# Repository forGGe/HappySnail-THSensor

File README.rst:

############################################################################
Happy Snail TH-Sensor: RS-485 ModBus Digital Temperature and Humidity Sensor
############################################################################

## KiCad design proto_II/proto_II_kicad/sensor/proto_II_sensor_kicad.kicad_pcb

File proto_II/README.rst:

###################################
Happy Snail TH-Sensor: Prototype II
###################################

*********************
Generating proper BOM
*********************

#. Install `KiBOM`_ tool. Instructions below assume that it was installed under ``~/project/KiBoM``
   directory.

#. Install `Interactive BOM tool`_. Instructions below assume that it was installed under
   ``~/projects/InteractiveHtmlBom/`` directory.

#. Generate `proto_II_assembly.xml` file by exporting any BOM from the KiCAD eeschema. This intermediate
   file is required for futher processing and there is no way to generate it without generating
   default KiCAD BOM.

#. Run from within ``proto_II_kicad/assembly`` directory::

     # Generic variant
     ~/projects/KiBoM/KiBOM_CLI.py ./proto_II_assembly.xml ./bom.csv

     # Only 5V, non-isolated RS485 variant
     ~/projects/KiBoM/KiBOM_CLI.py -r noiso_5v ./proto_II_assembly.xml ./bom.csv

     # Better 12V-24V, isolated RS485 variant
     ~/projects/KiBoM/KiBOM_CLI.py -r iso_12_24v ./proto_II_assembly.xml ./bom.csv

#. Generate BOM for importing into PartsBox::

     python ../../../scripts/process_bom.py ./bom.csv ./partsbox_bom.csv

#. Run from within ``proto_II_kicad/assembly`` directory to generate interactive BOM::

     python ~/projects/InteractiveHtmlBom/InteractiveHtmlBom/generate_interactive_bom.py \
       ./proto_II_assembly.kicad_pcb   \
       --netlist-file ./proto_II_assembly.xml \
       --extra-fields "MPN"

.. _`KiBOM`: https://github.com/SchrodingersGat/KiBoM
.. _`Interactive BOM tool`: https://github.com/openscopeproject/InteractiveHtmlBom

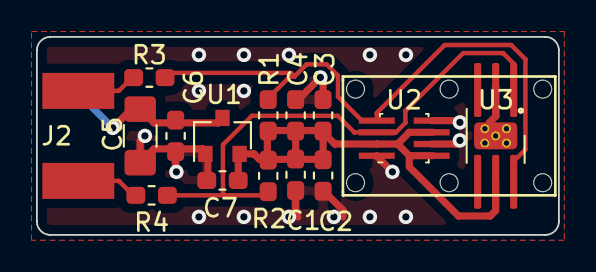
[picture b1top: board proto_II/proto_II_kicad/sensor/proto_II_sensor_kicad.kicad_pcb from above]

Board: 2 copper layers, 29.0 x 11.0 mm, 16 parts (1 on the bottom side), 7 nets.

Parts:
C1, C4: 100n; C_0603_1608Metric_Pad1.05x0.95mm_HandSolder
C2, C3: 10n; C_0603_1608Metric_Pad1.05x0.95mm_HandSolder
C5: 10u; C_1206_3216Metric_Pad1.42x1.75mm_HandSolder
C6, C7: 1u; C_0603_1608Metric_Pad1.05x0.95mm_HandSolder
J1, J2: Conn_01x02; PAD_2
R1, R2: 4K7; R_0603_1608Metric_Pad1.05x0.95mm_HandSolder
R3, R4: TERM; R_0603_1608Metric_Pad1.05x0.95mm_HandSolder
U1: XC6206P332MR; SOT-23
U2: BME280; Bosch_LGA-8_2.5x2.5mm_P0.65mm_ClockwisePinNumbering_HandSol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
U3: Si7020-A20; DFN-6-1EP_3x3mm_P1mm_EP1.5x2.4mm_HandSoldering

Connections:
+3V3: C1.1, C2.1, C3.1, C4.1, C7.1, R1.1, R2.1, U1.2, U2.2, U2.6, U2.8, U3.5
+5V: C5.1, C6.1, J1.1, U1.3
/SCL: J2.1, R3.1
/SCL_IC: R1.2, R3.2, U2.4, U3.6
/SDA: J2.2, R4.1
/SDA_IC: R2.2, R4.2, U2.3, U3.1
GND: C1.2, C2.2, C3.2, C4.2, C5.2, C6.2, C7.2, J1.2, U1.1, U2.1, U2.5, U2.7, U3.2, U3.7

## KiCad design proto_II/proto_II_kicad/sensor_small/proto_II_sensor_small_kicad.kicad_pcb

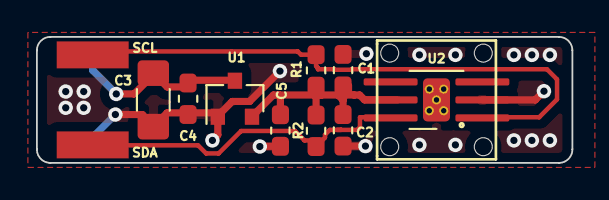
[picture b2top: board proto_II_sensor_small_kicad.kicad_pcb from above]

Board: 2 copper layers, 29.8 x 7.0 mm, 11 parts (1 on the bottom side), 5 nets.

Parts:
C1: 100n; C_0603_1608Metric_Pad1.05x0.95mm_HandSolder
C2: 10n; C_0603_1608Metric_Pad1.05x0.95mm_HandSolder
C3: 10u; C_1206_3216Metric_Pad1.42x1.75mm_HandSolder
C4, C5: 1u; C_0603_1608Metric_Pad1.05x0.95mm_HandSolder
J1: PWR_CONN; PAD_2_small
J2: I2C_CONN; PAD_2_small
R1, R2: 4K7; R_0603_1608Metric_Pad1.05x0.95mm_HandSolder
U1: XC6206P332MR; SOT-23
U2: Si7020-A20; DFN-6-1EP_3x3mm_P1mm_EP1.5x2.4mm_HandSoldering

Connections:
+3V3: C1.1, C2.1, C5.1, R1.1, R2.1, U1.2, U2.5
+5V: C3.1, C4.1, J1.1, U1.3
/SCL: J2.1, R1.2, U2.1
/SDA: J2.2, R2.2, U2.6
GND: C1.2, C2.2, C3.2, C4.2, C5.2, J1.2, U1.1, U2.2, U2.7

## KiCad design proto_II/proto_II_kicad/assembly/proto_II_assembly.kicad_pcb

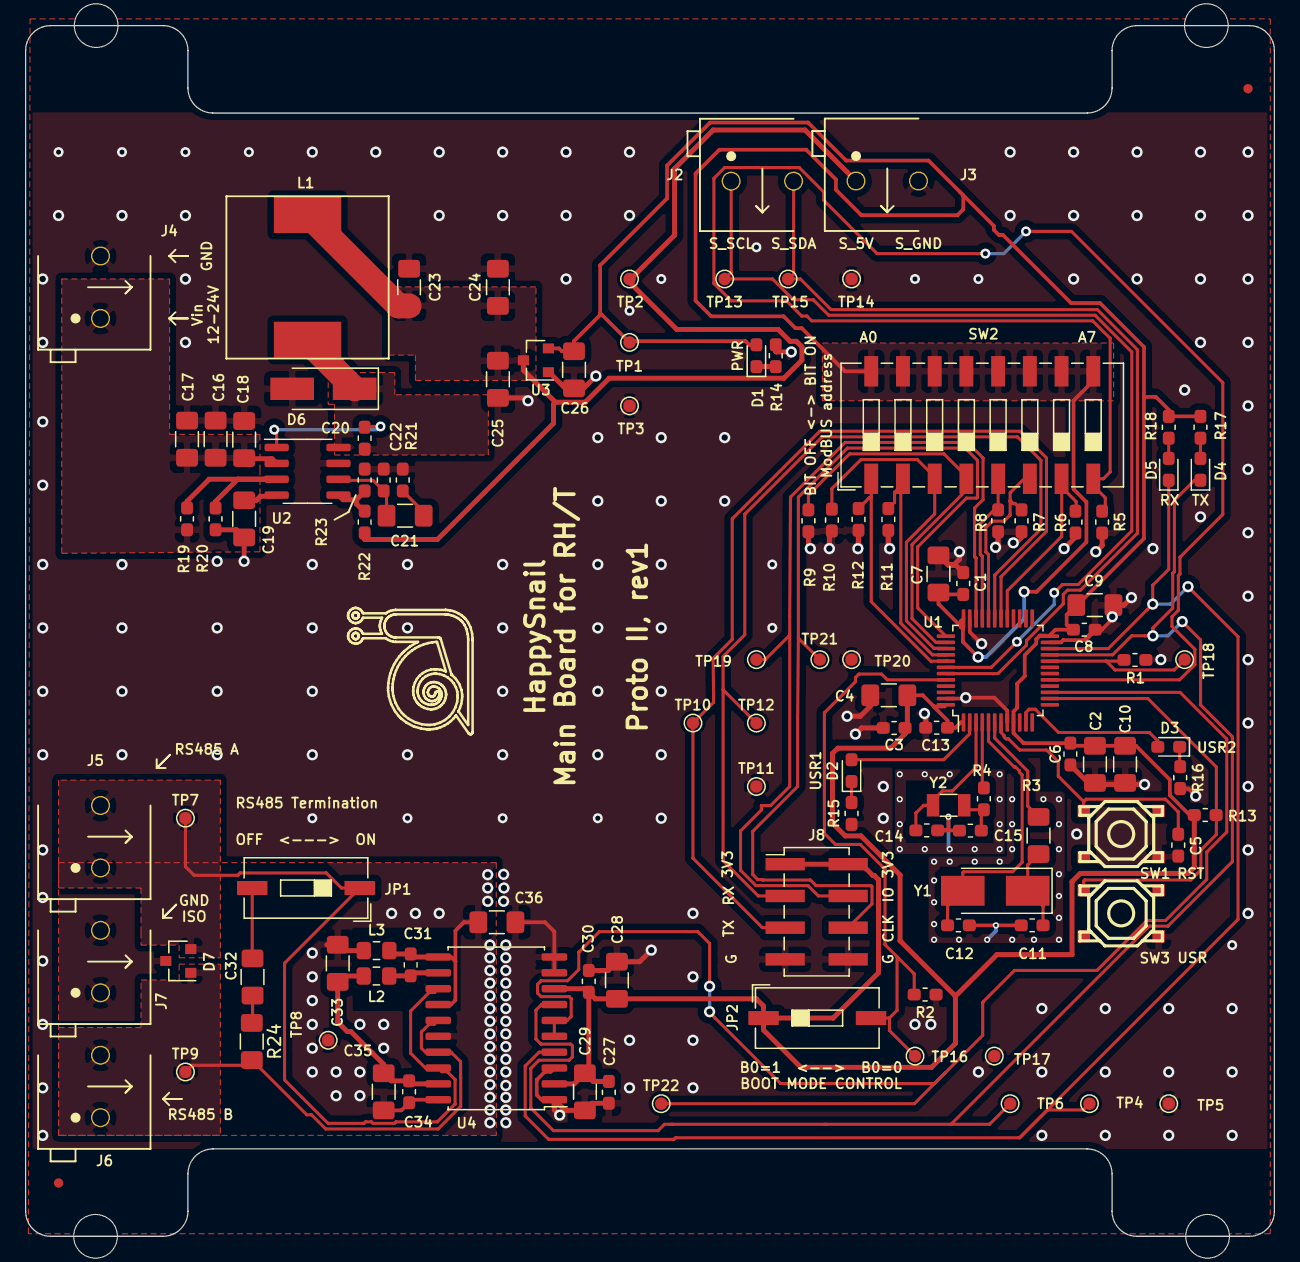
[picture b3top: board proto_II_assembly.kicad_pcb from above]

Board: 2 copper layers, 100.0 x 97.0 mm, 110 parts (0 on the bottom side), 52 nets.

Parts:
C1, C3, C5, C6, C8, C13, C20, C27, C30, C31, C34: 100n; C_0603_1608Metric_Pad1.05x0.95mm_HandSolder
C2, C4, C7, C9, C10, C25, C26: 1u; C_1206_3216Metric_Pad1.42x1.75mm_HandSolder
C11, C12: 30p; C_0603_1608Metric_Pad1.05x0.95mm_HandSolder
C14, C15, C22: 10p; C_0603_1608Metric_Pad1.05x0.95mm_HandSolder
C16, C17, C23, C24, C28, C33: 10u; C_1206_3216Metric_Pad1.42x1.75mm_HandSolder
C18, C19, C21, C29, C32, C35, C36: 10n; C_1206_3216Metric_Pad1.42x1.75mm_HandSolder
D1, D2, D3, D4, D5: BLUE_LED; D_0603_1608Metric_Pad1.05x0.95mm_HandSolder
D6: 700mV; D_SMA_Handsoldering
D7: SM712; SOT-23
J2: SNSR_I2C; DG300-5.0-02P-12
J3: SNSR_PWR; DG300-5.0-02P-12
J4: Vin; DG300-5.0-02P-12
J5: RS485_A; DG300-5.0-02P-12
J6: RS485_B; DG300-5.0-02P-12
J7: ISO_GND; DG300-5.0-02P-12
J8: SWD_DBG; PinHeader_2x04_P2.54mm_Vertical_SMD
JP1, JP2: JP; SW_DIP_SPSTx01_Slide_9.78x4.72mm_W8.61mm_P2.54mm
L1: 47u; SWRB1205S
L2, L3: FB; L_0805_2012Metric_Pad1.15x1.40mm_HandSolder
R1, R2, R5, R6, R7, R8, R9, R10, R11, R12, R13, R21, R22: 10K; R_0603_1608Metric_Pad1.05x0.95mm_HandSolder
R3: 560; R_1206_3216Metric_Pad1.42x1.75mm_HandSolder
R4: 0R; R_0603_1608Metric_Pad1.05x0.95mm_HandSolder
R14, R15, R16, R17, R18, R23: 2K2; R_0603_1608Metric_Pad1.05x0.95mm_HandSolder
R19: 220K; R_0603_1608Metric_Pad1.05x0.95mm_HandSolder
R20: 47K; R_0603_1608Metric_Pad1.05x0.95mm_HandSolder
R24: 120; R_1206_3216Metric_Pad1.42x1.75mm_HandSolder
SW1, SW3: PB; Tactile_Switch_5x5mm
SW2: MODBUS_ADDR; SW_DIP_SPSTx08_Slide_9.78x22.5mm_W8.61mm_P2.54mm
TP1: 3V3; TestPoint_Pad_D1.0mm
TP2: 5V; TestPoint_Pad_D1.0mm
TP3: G; TestPoint_Pad_D1.0mm
TP4: U2_RX; TestPoint_Pad_D1.0mm
TP5: G_U2; TestPoint_Pad_D1.0mm
TP6: U2_TX; TestPoint_Pad_D1.0mm
TP7: A; TestPoint_Pad_D1.0mm
TP8: G_ISO; TestPoint_Pad_D1.0mm
TP9: B; TestPoint_Pad_D1.0mm
TP10: U1_RX; TestPoint_Pad_D1.0mm
TP11, TP17, TP20: G_U1; TestPoint_Pad_D1.0mm
TP12: U1_TX; TestPoint_Pad_D1.0mm
TP13: SCL; TestPoint_Pad_D1.0mm
TP14: G_I2C; TestPoint_Pad_D1.0mm
TP15: SDA; TestPoint_Pad_D1.0mm
TP16, TP19: U1_B0; TestPoint_Pad_D1.0mm
TP18, TP21: U1_B1; TestPoint_Pad_D1.0mm
TP22: DE_RE; TestPoint_Pad_D1.0mm
U1: STM32F103C8Tx; LQFP-48_7x7mm_P0.5mm
U2: TPS54331; SOIC-8_3.9x4.9mm_P1.27mm
U3: XC6206P332MR; SOT-23
U4: ADM2587E; SOIC-20W_7.5x12.8mm_P1.27mm
Y1: HSE; Crystal_SMD_5032-2Pin_5.0x3.2mm_HandSoldering
Y2: LSE; Crystal_SMD_3215-2Pin_3.2x1.5mm

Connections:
+3V3: C1.1, C2.1, C3.1, C4.1, C6.1, C7.1, C8.1, C9.1, C10.1, C13.1, C26.1, C27.1, C28.1, C29.1, C30.1, D1.2, J8.1, J8.2, JP2.1, R13.2, R17.2, R18.2, SW2.9, SW2.10, SW2.11, SW2.12, SW2.13, SW2.14, SW2.15, SW2.16, TP1.1, U1.1, U1.9, U1.24, U1.36, U1.48, U3.2, U4.2, U4.8
+5V: C23.1, C24.1, C25.1, J3.1, L1.2, R22.1, TP2.1, U3.3
/BOOT0: JP2.2, R2.2, TP16.1, U1.44
/BOOT1: R1.1, TP18.1, U1.20
/DE~RE: TP22.1, U1.15, U4.5, U4.6
/I2C1_SCL: J2.1, TP13.1, U1.42
/I2C1_SDA: J2.2, TP15.1, U1.43
/MODBUS_A0: R12.1, SW2.1, U1.41
/MODBUS_A1: R11.1, SW2.2, U1.40
/MODBUS_A2: R10.1, SW2.3, U1.39
/MODBUS_A3: R9.1, SW2.4, U1.38
/MODBUS_A4: R8.1, SW2.5, U1.33
/MODBUS_A5: R7.1, SW2.6, U1.32
/MODBUS_A6: R6.1, SW2.7, U1.29
/MODBUS_A7: R5.1, SW2.8, U1.17
/NRST: C5.1, SW1.2, U1.7
/OSC32_IN: C14.2, U1.3, Y2.1
/OSC32_OUT: R4.1, U1.4
/OSC_IN: C12.1, U1.5, Y1.2
/OSC_OUT: R3.1, U1.6
/RS485_A: D7.2, J5.1, J5.2, JP1.1, TP7.1, U4.13, U4.18
/RS485_B: D7.1, J6.1, J6.2, R24.2, TP9.1, U4.15, U4.17
/SWDCLK: J8.6, TP21.1, U1.37
/SWDIO: J8.4, TP19.1, U1.34
/UART1_RX: J8.3, TP12.1, U1.31
/UART1_TX: J8.5, TP10.1, U1.30
/UART3_RX: D5.1, TP4.1, U1.22, U4.4
/UART3_TX: D4.1, TP6.1, U1.21, U4.7
/USR1_LED: D2.2, U1.2
/USR2_LED: D3.2, U1.11
/USR_BTN: R13.1, SW3.2, U1.14
/power/PH: C20.1, D6.1, L1.1, U2.8
/power/Vin: C16.1, C17.1, C18.1, J4.1, R19.1, U2.2
/rs485/ISO_IN: C33.1, C34.1, C35.1, L2.2, U4.19
/rs485/ISO_OUT: C31.1, L2.1, U4.12
GND: C1.2, C2.2, C3.2, C4.2, C5.2, C6.2, C7.2, C8.2, C9.2, C10.2, C11.2, C12.2, C13.2, C14.1, C15.1, C16.2, C17.2, C18.2, C19.2, C22.2, C23.2, C24.2, C25.2, C26.2, C27.2, C28.2, C29.2, C30.2, C36.1, D6.2, J3.2, J4.2, J8.7, J8.8, R1.2, R2.1, R5.2, R6.2, R7.2, R8.2, R9.2, R10.2, R11.2, R12.2, R14.2, R15.2, R16.2, R20.2, R21.2, R23.2, SW1.1, SW3.1, TP3.1, TP5.1, TP11.1, TP14.1, TP17.1, TP20.1, U1.8, U1.23, U1.35, U1.47, U2.7, U3.1, U4.1, U4.3, U4.9, U4.10
GNDD: C31.2, C33.2, C34.2, C35.2, C36.2, D7.3, J7.1, J7.2, L3.1, L3.2, TP8.1, U4.11, U4.14, U4.16, U4.20
unnamed: C11.1, R3.2, Y1.1
unnamed: C15.2, R4.2, Y2.2
unnamed: C19.1, U2.4
unnamed: C20.2, U2.1
unnamed: C21.1, C22.1, U2.6
unnamed: C21.2, R21.1
unnamed: C32.1, R24.1
unnamed: C32.2, JP1.2
unnamed: D1.1, R14.1
unnamed: D2.1, R15.1
unnamed: D3.1, R16.1
unnamed: D4.2, R17.1
unnamed: D5.2, R18.1
unnamed: R19.2, R20.1, U2.3
unnamed: R22.2, R23.1, U2.5

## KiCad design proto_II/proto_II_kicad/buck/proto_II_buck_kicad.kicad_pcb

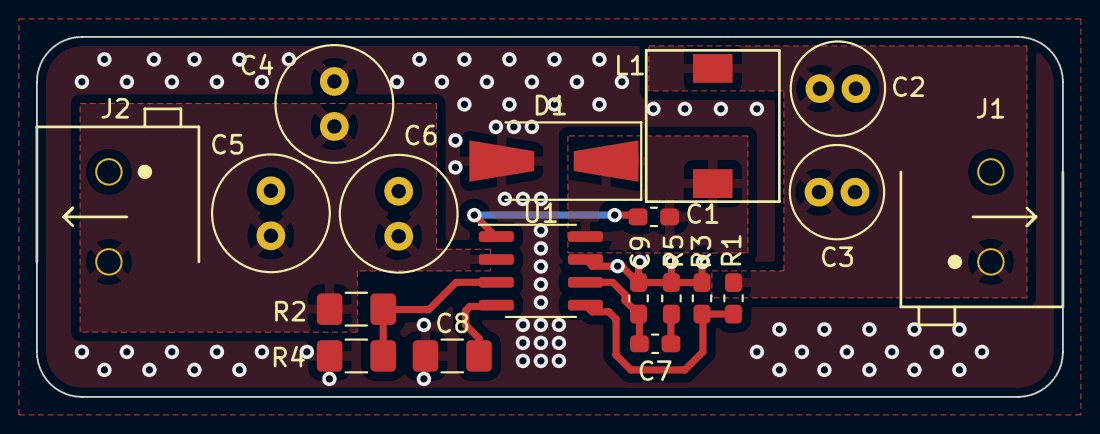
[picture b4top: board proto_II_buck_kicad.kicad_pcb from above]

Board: 2 copper layers, 57.0 x 20.0 mm, 19 parts (0 on the bottom side), 10 nets.

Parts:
C1: 100n; C_0603_1608Metric_Pad1.05x0.95mm_HandSolder
C2, C3: 47u; C_Radial_D5.0mm_H11.0mm_P2.00mm
C4, C5: 10u; C_Radial_D6.3mm_H11.0mm_P2.50mm
C6: 10n; C_Radial_D6.3mm_H11.0mm_P2.50mm
C7: 2n2; C_0603_1608Metric_Pad1.05x0.95mm_HandSolder
C8: 10n; C_1206_3216Metric_Pad1.42x1.75mm_HandSolder
C9: 10p; C_0603_1608Metric_Pad1.05x0.95mm_HandSolder
D1: 700mV; D_SMA-SMB_Universal_Handsoldering
J1: VDC_OUT; DG300-5.0-02P-12
J2: VDC_IN; DG300-5.0-02P-12
L1: 22u; CDRH74
R1: 10K; R_0603_1608Metric_Pad1.05x0.95mm_HandSolder
R2: 220K; R_1206_3216Metric_Pad1.42x1.75mm_HandSolder
R3: 2K2; R_0603_1608Metric_Pad1.05x0.95mm_HandSolder
R4: 47K; R_1206_3216Metric_Pad1.42x1.75mm_HandSolder
R5: 13K3; R_0603_1608Metric_Pad1.05x0.95mm_HandSolder
U1: TPS54331; SOIC-8_3.9x4.9mm_P1.27mm

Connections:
/PH: C1.1, D1.1, L1.1, U1.8
/VIN: C4.1, C5.1, C6.1, J2.2, R2.1, U1.2
/VOUT: C2.1, C3.1, J1.1, L1.2, R1.1
GND: C2.2, C3.2, C4.2, C5.2, C6.2, C8.2, C9.2, D1.2, J1.2, J2.1, R3.2, R4.2, R5.2, U1.7
unnamed: C1.2, U1.1
unnamed: C7.1, C9.1, U1.6
unnamed: C7.2, R5.1
unnamed: C8.1, U1.4
unnamed: R1.2, R3.1, U1.5
unnamed: R2.2, R4.1, U1.3

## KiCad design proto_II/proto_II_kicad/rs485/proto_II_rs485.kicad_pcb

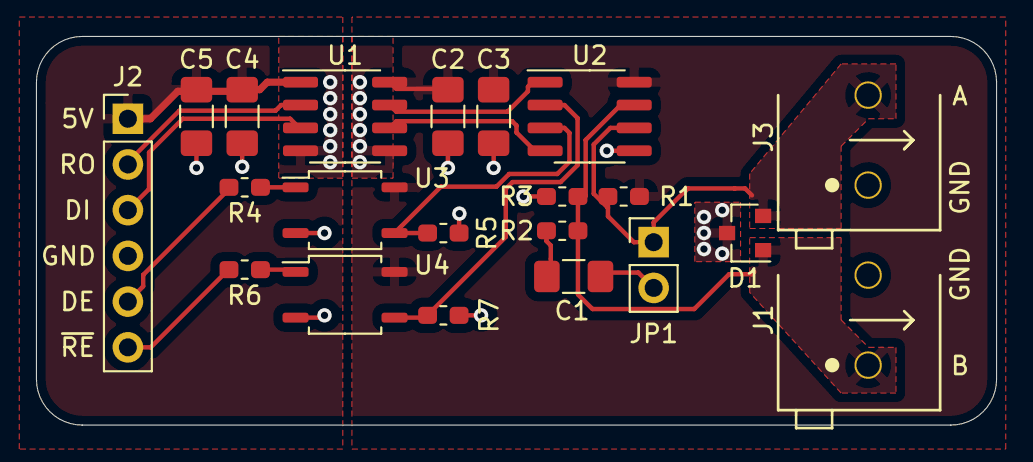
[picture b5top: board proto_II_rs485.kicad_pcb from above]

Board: 2 copper layers, 53.3 x 21.6 mm, 21 parts (0 on the bottom side), 18 nets.

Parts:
C1: 10n; C_1206_3216Metric_Pad1.42x1.75mm_HandSolder
C2, C4: 100n; C_1206_3216Metric_Pad1.42x1.75mm_HandSolder
C3, C5: 1u; C_1206_3216Metric_Pad1.42x1.75mm_HandSolder
D1: SM712; SOT-23
J1: A_CONN; DG300-5.0-02P-12
J2: INPUT; PinHeader_1x06_P2.54mm_Vertical
J3: B_CONN; DG300-5.0-02P-12
JP1: JP; PinHeader_1x02_P2.54mm_Vertical
R1, R3, R4, R6: 2K2; R_0603_1608Metric_Pad1.05x0.95mm_HandSolder
R2: 120; R_0603_1608Metric_Pad1.05x0.95mm_HandSolder
R5, R7: 10K; R_0603_1608Metric_Pad1.05x0.95mm_HandSolder
U1: ADUM5241; SOIC-8_3.9x4.9mm_P1.27mm
U2: ST485EBDR; SOIC-8_3.9x4.9mm_P1.27mm
U3, U4: EL357N-G; SOP-4_3.8x4.1mm_P2.54mm

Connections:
+5V: C4.1, C5.1, J2.1, U1.1
+5VD: C2.1, C3.1, R1.2, U1.8, U2.8, U3.4, U4.4
/A: D1.2, J3.2, JP1.1, R1.1, U2.6
/B: D1.1, J1.1, R2.2, R3.2, U2.7
/DE: J2.5, R4.2
/DI: J2.3, U1.3
/RO: J2.2, U1.2
/~RE: J2.6, R6.2
GND: C4.2, C5.2, J2.4, U1.4, U3.2, U4.2
GNDD: C2.2, C3.2, D1.3, J1.2, J3.1, R3.1, R5.1, R7.1, U1.5, U2.5
unnamed: C1.1, R2.1
unnamed: C1.2, JP1.2
unnamed: R4.1, U3.1
unnamed: R5.2, U2.3, U3.3
unnamed: R6.1, U4.1
unnamed: R7.2, U2.2, U4.3
unnamed: U1.6, U2.4
unnamed: U1.7, U2.1

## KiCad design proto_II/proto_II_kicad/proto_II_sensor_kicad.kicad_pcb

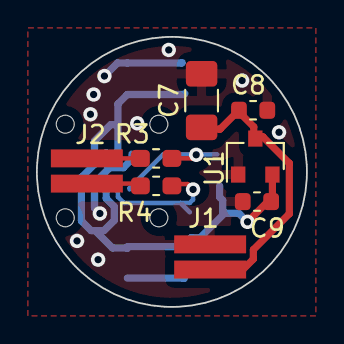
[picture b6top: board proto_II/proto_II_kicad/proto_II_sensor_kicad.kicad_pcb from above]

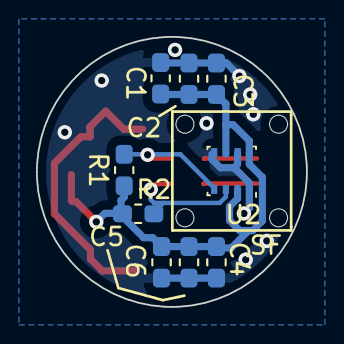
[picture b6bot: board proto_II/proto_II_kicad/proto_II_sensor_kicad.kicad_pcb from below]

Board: 2 copper layers, 15.0 x 15.0 mm, 18 parts (10 on the bottom side), 7 nets.

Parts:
C1, C6: 1u; C_0603_1608Metric_Pad1.05x0.95mm_HandSolder
C2, C5: 100n; C_0603_1608Metric_Pad1.05x0.95mm_HandSolder
C3, C4: 10n; C_0603_1608Metric_Pad1.05x0.95mm_HandSolder
C7: 10u; C_1206_3216Metric_Pad1.42x1.75mm_HandSolder
C8, C9: 1u; C_0603_1608Metric
J1, J2: Conn_01x02; PAD_2
R1, R2: 4K7; R_0603_1608Metric_Pad1.05x0.95mm_HandSolder
R3, R4: TERM; R_0603_1608Metric_Pad1.05x0.95mm_HandSolder
SF: SF2-CAP; SENSIRION-SF2
U1: XC6206P332MR; SOT-23
U2: BME280; Bosch_LGA-8_2.5x2.5mm_P0.65mm_ClockwisePinNumbering

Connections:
+3V3: C1.1, C2.1, C3.1, C4.1, C5.1, C6.1, C9.1, R1.1, R2.1, U1.2, U2.2, U2.6, U2.8
+5V: C7.1, C8.1, J1.1, U1.3
GND: C1.2, C2.2, C3.2, C4.2, C5.2, C6.2, C7.2, C8.2, C9.2, J1.2, U1.1, U2.1, U2.5, U2.7
unnamed: J2.1, R3.1
unnamed: J2.2, R4.1
unnamed: R1.2, R3.2, U2.4
unnamed: R2.2, R4.2, U2.3

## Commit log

2019-06-16 Add prototype I subproject tree and basic schematic
2019-06-16 PC13 blink code
2019-06-16 RS485 reading and writing
2019-06-19 Zephyr-based BAT placeholder
    Previous stuff moved to .attic
2019-06-21 Extended BAT with rough modbus ASCII parser
2019-06-23 Complete BAT code
2019-06-23 Complete BAT schematics
2019-06-30 Proto II: basic circuit around TPS54331, not computed yet
    Values of components to be computed later.
2019-07-02 Re-wire switching power supply and add sensor sub-project
    Switching regulator re-wired according to guidelines.
    Still, freq compensation values must be re-calculated.
    Sensor sub-project is added. Its purpose to deliver small PCB
    board, where sensor is soldered and sealed.
2019-07-07 Proto II: route for sensor board
    Add libraries and footprints for SF2 cap and simple PAD connector for
    soldering wires
2019-07-09 Proto II: route buck converter sub-board
    Additionally:
    - Made footprint for inductor and found 3d-model for that
    - Add missing PCB and netlist for sensor sub-board (see previous commit)
    - Couple of addtions for existing footprints (SF2, PAD, etc.)A
    - Update gitignore to ignore cache KiCAD files
2019-07-09 Proto II: panelized sensor and buck board, order from JLCPCB
    + gerber files
2019-07-12 Proto II: cleanup and move project to separate dirs
    Common library is substituted. Gerber files are updated to match what
    sent to JLCPCB
2019-07-17 Proto II: RS485 isolated module board
2019-07-18 Proto II: RS485 isolated module board, order from JLCPCB
2019-08-08 Capture real part information into the schematic
2019-08-16 Rework sensor board: allow hand-soldering of sensor
    Additional sensor is used with easier footprint: Si70XX series
2019-08-17 Rework sensor board: gerber files
2019-08-17 Fix bug: spurious character led to infinite ModBus response
    + add script to read values and send them to TB
2019-09-16 8mm sensor PCB
2019-09-16 BAT code for Si7006
2019-09-18 Update instructions on flashing and using board for BAT tests
2019-09-19 Fix table rendering: missing whitspace in README for proto I
2019-09-19 Add arguments for publishing script to use custom TB credentials
2019-09-30 Draft of assembled proto II
2019-10-01 Draft of assembled proto II: optimize BOM and put all logic components
2019-10-02 Draft of assembled proto II: finalized BOM
2019-10-07 proto II: finish draft routing
2019-10-07 proto II: add more pin designators to silkscreen
2019-10-18 proto I: migrate to Zephyr v2.0.0 and improve send script
    Add argparse to script. Move to SI7006 driver built in Zephyr.
2019-10-19 proto I: add MCU temperature reporting
2019-11-14 Better file management for git <-> kicad
2019-11-14 Better field naming for components
2019-11-14 Add old library file that was previously forgotten
2019-11-15 Add boards variants and BOM processing script
2019-11-17 Add placeholder for Proto II sources
2019-11-17 Baisis for new Modbus ASCII library
2019-11-17 Add unit test skeleton
2019-11-17 tmp: modbus lib
2019-12-29 tmp: making rev1 started
2019-12-29 tmp: more work
2020-01-05 tmp: more fixes
2020-01-08 tmp: layout started
2020-01-08 tmp: last bit of changes
2020-01-09 Fix issues with rev.0 of MarkI board
    Partially addresses #16
2020-02-05 Rename libraries and footprints to better match future repo split
2020-02-05 Update client projects to work with updated libs
2020-02-05 Move common libraries to common repo
2020-02-05 Add peru file to manage common libraries
2020-02-07 Fix revision of common lib
